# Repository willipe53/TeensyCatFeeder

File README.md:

# TeensyCatFeeder

Instructions for an Teensy 4.0 controller to lock a cover over a catfood dish with an electromagnet when a button is pressed, and to move a servo arm to reveal the catfood (and ring a bell) at a scheduled time in the morning.

This is a project that I originally did using Raspberry Pi, then ported to ESP32, then to Teensy.  Hardware consists of the microcontroller, a 5V relay with a transistor circuit to control the electromagnet, a button, and a small LCD display.

There are three servos connected in an arm that hold the lid (a wood box) over dish with catfood. See [sketch.png](sketch.png).  In the code, the servos are named Shoulder, Elbow and Wrist.  See [ServoControl.ino](ServoControl.ino).  Their relative positions are saved in non-volatile memory on the controller using the [Preferences.h](https://github.com/espressif/arduino-esp32/tree/master/libraries/Preferences) library. See [SavingPrefs.ino](SavingPrefs.ino).

There is only one button, so it is hopelessly overloaded.  A short press either opens the feeder or locks the magnet, depending upon current state.  A long press cycles through current time and feeding time, so they can be set.  You can also connect the feeder to a computer and set these values via the serial monitor.  Sending a `p` over the serial port should show the current values, as well as the following menu:

`o - Open the lid`
`l - Lock or unlock magnet (1 or 0)`
`s - Move shoulder to x`
`e - Move elbow to x`
`w - Move wrist to x`
`j - Save number of jiggles to x`
`t - Save wake time as x (HHMM) - 0 = off`
`d - Save clock date as x (YYYYMMDD)`
`c - Save clock time as x (HHMM)`
`b - Save as new open`
`p - Print all values`

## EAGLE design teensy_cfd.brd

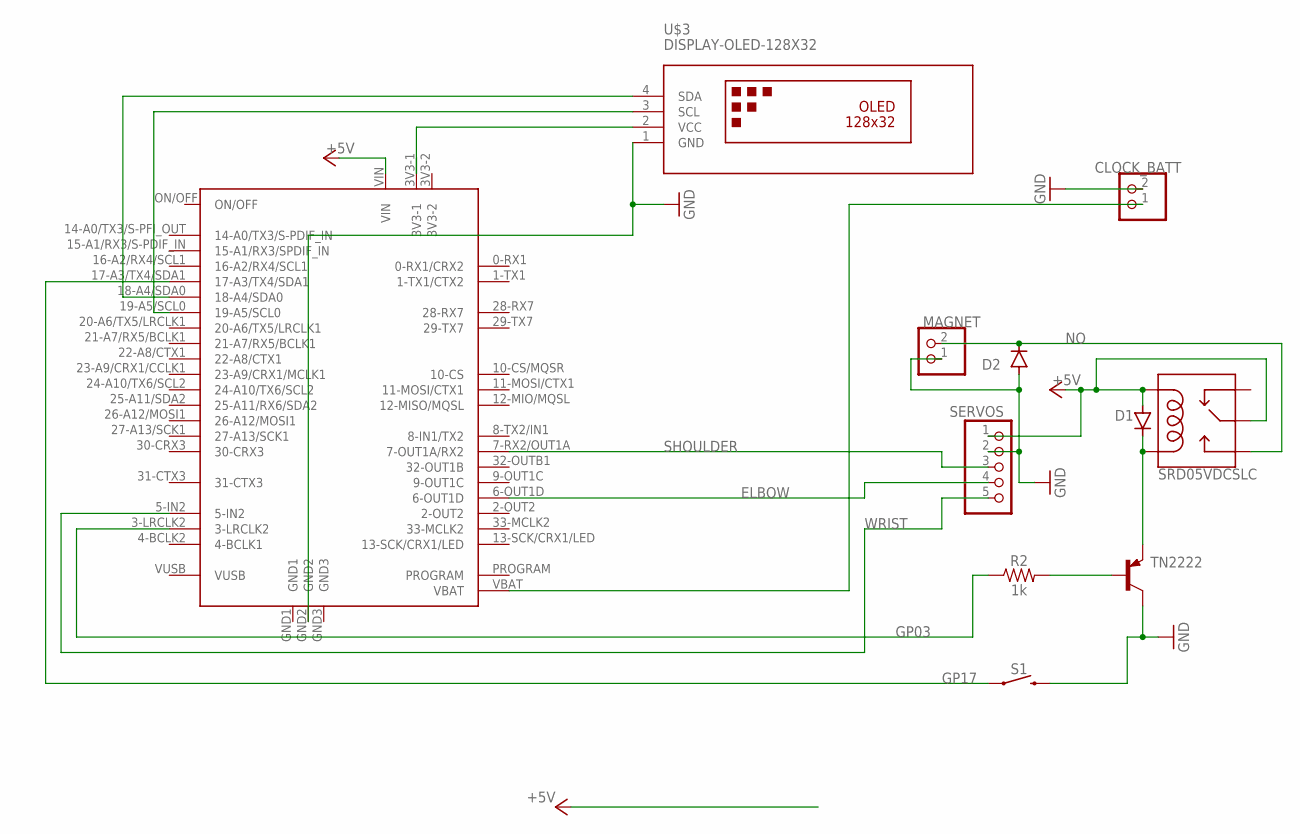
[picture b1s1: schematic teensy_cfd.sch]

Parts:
CLOCK_BATT: PINHD-1X2; 1X02
D1, D2: 1N4004; DO41-10
MAGNET: PINHD-1X2; 1X02
R2: 1k; AXIAL-0.3
S1: MOMENTARY-SWITCH-SPST-PTH-6.0MM; TACTILE_SWITCH_PTH_6.0MM
SERVOS: PINHD-1X5; 1X05
SRD05VDCSLC: RELAYPTH; SRD-05VDC-SL-C
TN2222: TN2222; TO92
U$1: TEENSY40
U$3: DISPLAY-OLED-128X32

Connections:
+5V: D1.A, SERVOS.1, SRD05VDCSLC.COIL1, SRD05VDCSLC.SWCOMMON, U$1.VIN
ELBOW: SERVOS.4, U$1.6-OUT1D
GND: CLOCK_BATT.2, D2.A, MAGNET.1, S1.3 (2), SERVOS.2, TN2222.1 (C), U$1.GND2, U$3.1 (GND)
GP03: R2.P$1 (1), U$1.3-LRCLK2
GP17: S1.1, U$1.17-A3/TX4/SDA1
unnamed: R2.P$2 (2), TN2222.2 (B)
unnamed: D1.C, SRD05VDCSLC.COIL0, TN2222.3 (E)
unnamed: CLOCK_BATT.1, U$1.VBAT
unnamed: U$1.18-A4/SDA0, U$3.4 (SDA)
unnamed: U$1.19-A5/SCL0, U$3.3 (SCL)
unnamed: U$1.3V3-1, U$3.2 (VCC)
NO: D2.C, MAGNET.2, SRD05VDCSLC.SWOPEN
SHOULDER: SERVOS.3, U$1.7-RX2/OUT1A (7-OUT1A/RX2)
WRIST: SERVOS.5, U$1.5-IN2

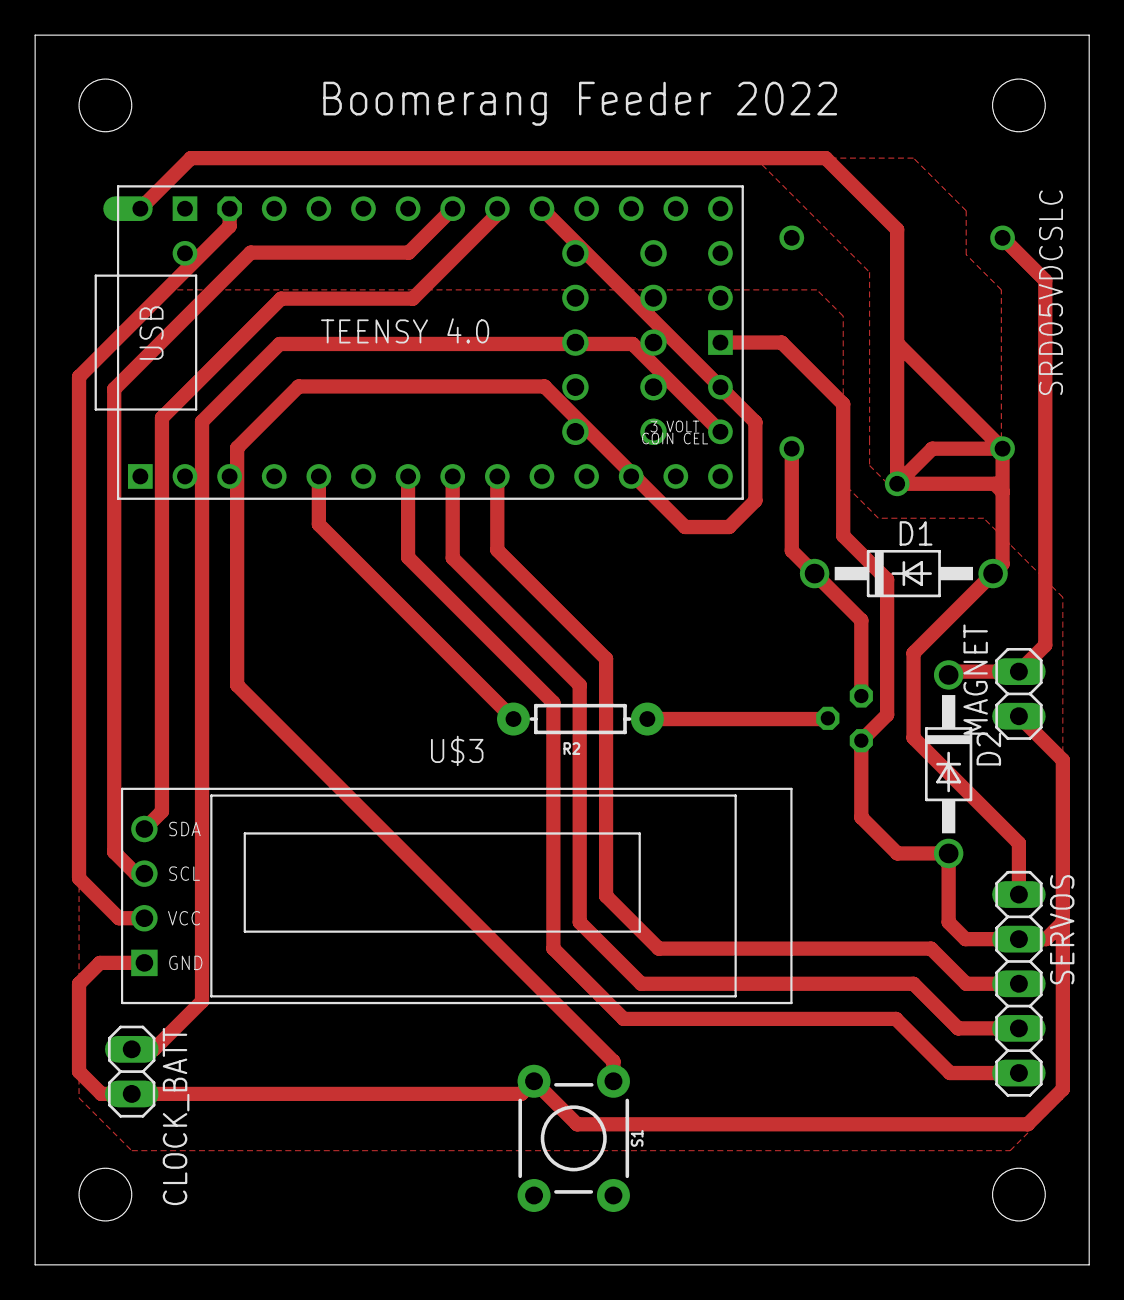
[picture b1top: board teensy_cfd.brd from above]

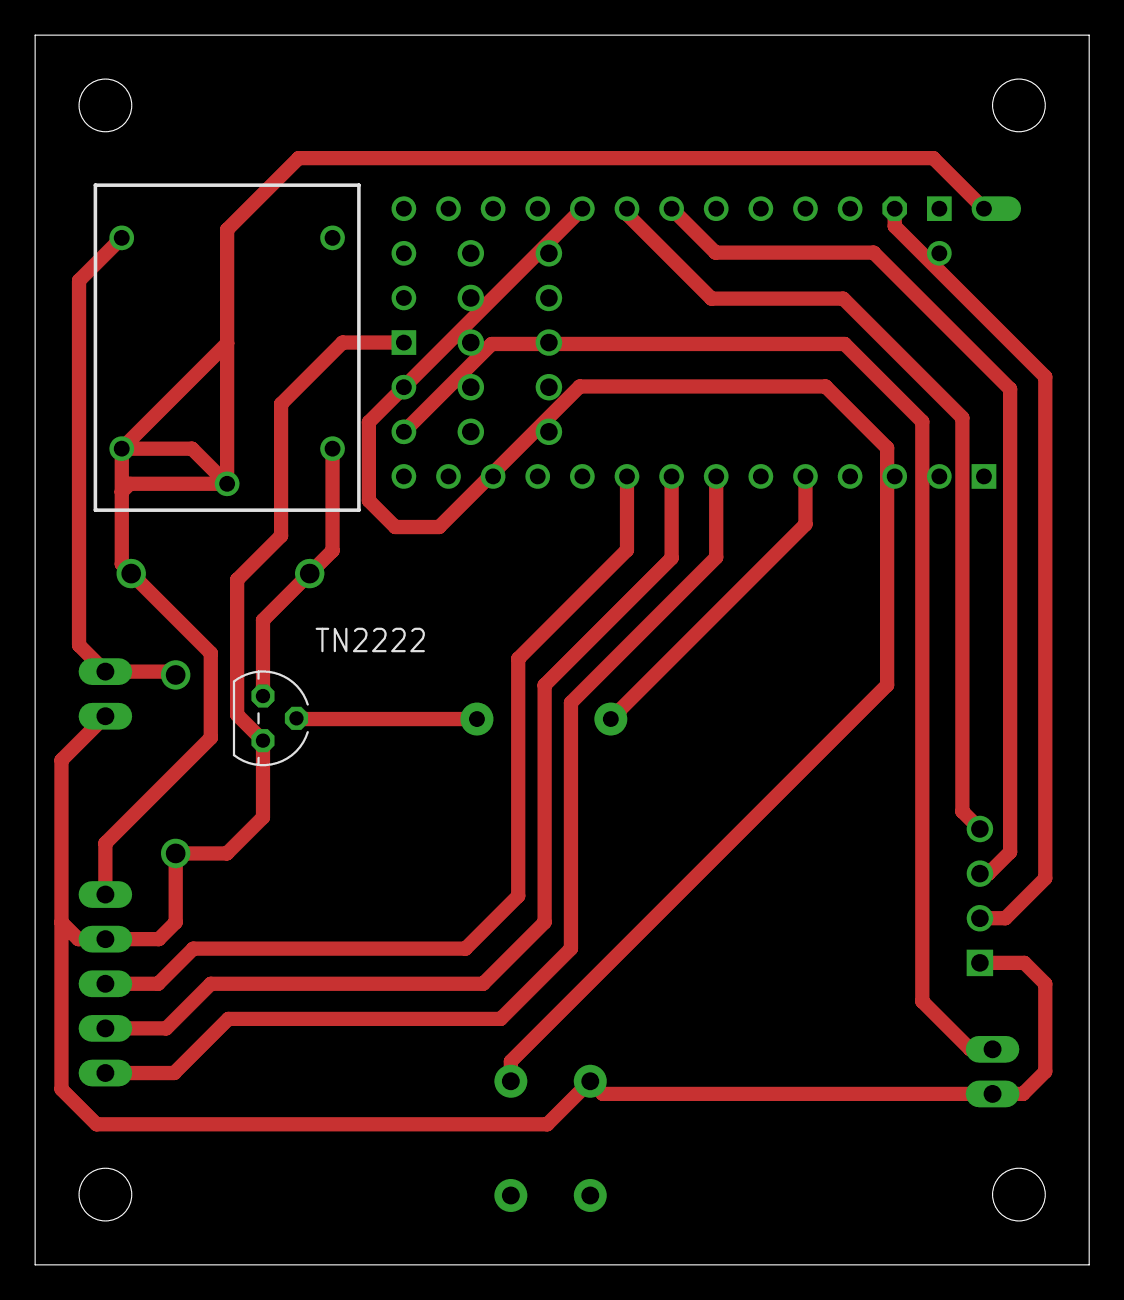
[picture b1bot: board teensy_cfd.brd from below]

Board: 2 copper layers, 60.0 x 70.0 mm, 11 parts (2 on the bottom side), 14 nets.

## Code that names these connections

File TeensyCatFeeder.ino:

#include <EEPROM.h>
#include <TimeLib.h>
#include <Servo.h>
#include <Adafruit_GFX.h>
#include <Adafruit_SSD1306.h>
#include <Wire.h>
#include <EEPROM.h>

#define SCREEN_WIDTH  128 // pixels
#define SCREEN_HEIGHT  32 
#define PRESS_TIME   1000 // milliseconds
#define BUTTON         17 // GPIO
#define MAGNET          3
#define SHOULDER        0 //array index
#define ELBOW           1
#define WRIST           2
#define TS_NONE         0
#define TS_WAKE         1
#define TS_HOUR         2
#define TS_MIN          3
#define DIM_SCREEN     20 //after 20 seconds
 
//default preferences
int servoTop         = 2500; //milliseconds
int servoBottom      = 1400;
int servoMiddle      = 1400;
int servoSide        =  500;
int servoElbowOffset =  250;
int jiggleTimes      =    3;
int wakeTime         =  500; //5AM, wake time of 0 means vacation mode, no feeding

struct Prefs {
  int servoTop;
  int servoBottom;
  int servoMiddle;
  int servoSide;
  int servoElbowOffset;
  int jiggleTimes;
  int wakeTime;
};
Prefs prefs;

Adafruit_SSD1306 display(SCREEN_WIDTH, SCREEN_HEIGHT, &Wire, -1, 1000000);
Servo shoulderServo;
Servo elbowServo;
Servo wristServo;
Servo servoMotor[] = {shoulderServo, elbowServo, wristServo};

int servoPins[]     = {7, 6, 5};
String servoNames[] = {"Shoulder", "Elbow", "Wrist"};
char lastTimeStr[128];
int cursorPos = 130; //just offscreen
int lastButtonState = LOW;
int thisButtonState;
int timeSetMode = TS_NONE;
unsigned long pressedTime  = 0;
unsigned long releasedTime = 0;
unsigned long sleepDisplayAt;
bool servosOn = false;
bool isPressing = false;
bool isLongDetected = false;
bool isLocked = false;
bool displayAwake = true;
bool doneForToday = false;

String inputChars = "olsewjtdcbp";
String outputNames[] = {"Open the lid",                            //o
                        "Lock or unlock magnet (1 or 0)",          //l
                        "Move shoulder to x",                      //s
                        "Move elbow to x",                         //e
                        "Move wrist to x",                         //w
                        "Save number of jiggles to x",             //j
                        "Save wake time as x (HHMM) - 0 = off",    //t
                        "Save clock date as x (YYYYMMDD))",        //d
                        "Save clock time as x (HHMM))",            //c
                        "Save as new open",                        //b
                        "Print all values"};                       //p

void processCommand(String cmd) {
  Serial.printf("Command received: %s\n", cmd.c_str());
  String key = cmd.substring(0,1);
  long valu = cmd.substring(1,cmd.length()-1).toInt();
  if (key.equals("o")) openLid();   
  else if (key.equals("l")) toggleMagnet(valu);            
  else if (key.equals("s")) moveServo(SHOULDER, valu);   
  else if (key.equals("e")) moveServo(ELBOW, valu);   
  else if (key.equals("w")) moveServo(WRIST, valu);   
  else if (key.equals("j")) saveJiggleTimes(valu);   
  else if (key.equals("t")) saveWakeTime(valu);            
  else if (key.equals("d")) resetDateTo(valu);            
  else if (key.equals("c")) resetTimeTo(valu);            
  else if (key.equals("b")) saveNewOpenPosition();   
  else if (key.equals("p")) printValues();            
  else Serial.printf("Unrecognized input: no values will be changed\n");
}

void startDisplayDimmerTimer() {
  sleepDisplayAt = millis() + (DIM_SCREEN * 1000); 
  displayAwake = true;
  Serial.printf("Now: %d, sleep set for: %d\n", millis(), sleepDisplayAt);
}

void resetDateTo(long valu) {
  String cmd = String(valu);
  int yr = cmd.substring(0,4).toInt();
  int mo = cmd.substring(4,6).toInt();
  int dd = cmd.substring(6,8).toInt();  
  setTime(hour(),minute(),0,dd,mo,yr);
}

void resetTimeTo(long valu) {
  String cmd = String(valu);
  int hr = cmd.substring(0,2).toInt();
  int mn = cmd.substring(2,4).toInt();
  setTime(hr,mn,0,day(),month(),year());
//  Serial.printf("valu:%d yr:%d mo%d dd%d hr%d mn%d\n", valu, yr, mo, dd, hr, mn);
}

time_t getTeensy3Time() {
  return Teensy3Clock.get();
}

void toggleMagnet(int valu) {
  digitalWrite(MAGNET, valu);
  isLocked = valu;
  Serial.printf("Reset magnet to %d\n", isLocked);
}

bool isWakeupTime() {
  if (wakeTime == 0) return false;
  if ((hour() == getWakeHour()) && (minute() >= getWakeMin()) && (doneForToday == false)) {
    doneForToday = true;
    return true;
  }
  return false;
}

int getWakeHour() {
  return (wakeTime / 100);
}

int getWakeMin() {
  return (wakeTime % 100);
}

void advanceDigit() {
  if (timeSetMode == TS_HOUR) {
    int hr = hour() + 1;
    if (hr > 24) hr = 1;
    setTime(hr,minute(),0,day(),month(),year());
  } else if (timeSetMode == TS_MIN) {
    int mn = minute() + 1;
    if (mn > 59) mn = 0;
    setTime(hour(),mn,0,day(),month(),year());
  } else if (timeSetMode == TS_WAKE) {
    int wake = getWakeHour() + 1;
    if (wake > 24) wake = 0;
    saveWakeTime(wake*100);  
  }
  Serial.printf("Advancing the setting under the cursor for time item %d.", timeSetMode);
}

void setup()  {
  Serial.begin(9600);
  loadPreferences(true);
  pinMode(BUTTON, INPUT_PULLUP);
  pinMode(MAGNET, OUTPUT);
  for (int i=0; i<3; i++) {
    pinMode(servoPins[i], OUTPUT);
    digitalWrite(servoPins[i], 0);
  }
  toggleMagnet(0);
  setSyncProvider(getTeensy3Time);
  display.begin(SSD1306_SWITCHCAPVCC, 0x3C);
  display.setTextSize(1);
  display.setTextColor(WHITE);
  printValues();
  startDisplayDimmerTimer();
}

void loop() {
  //see if it is time to open the arm
  if (isWakeupTime()) openLid();

  //advance to tomorrow, if an hour past since last feeding
  if (doneForToday && (hour() >= getWakeHour()+1)) doneForToday = false;
  
  //turn off display to avoid burn in
  if (millis() > sleepDisplayAt) displayAwake = false;
  
  //check button
  thisButtonState = digitalRead(BUTTON);
  if (lastButtonState == HIGH && thisButtonState == LOW) {        // button is pressed
    pressedTime = millis();
    isPressing = true;
    isLongDetected = false;
  } else if (lastButtonState == LOW && thisButtonState == HIGH) { // button is released
    isPressing = false;
    releasedTime = millis();
    long pressDuration = releasedTime - pressedTime;
    if (pressDuration < PRESS_TIME) {
      Serial.println("A short press is detected");
      if (!displayAwake) startDisplayDimmerTimer();
      else if (timeSetMode > TS_NONE) advanceDigit();
      else if (isLocked) openLid();
      else toggleMagnet(1);
    }
  }
  if (isPressing == true && isLongDetected == false) {
    long pressDuration = millis() - pressedTime;
    if (pressDuration > PRESS_TIME) {
      Serial.println("A long press is detected");
      isLongDetected = true;
      if (timeSetMode == TS_WAKE) {
        timeSetMode = TS_NONE;
      } else {
        timeSetMode++;
      }
      Serial.printf("Switching to time set mode %d.\n", timeSetMode);
    }
  }
  lastButtonState = thisButtonState;

  //drive display
  display.clearDisplay();
  drawLock();
  drawWake();
  drawTime();
  display.display();

  //manual testing
  if (Serial.available() > 0) processCommand(Serial.readString());

}

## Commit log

2022-03-17 Initial working display and button
2022-03-18 Working servos
2022-03-18 Working servos and prefs
2022-03-19 Scheduler working
2022-03-19 Added onscreen time set
2022-03-19 Added vacation mode
2022-03-19 Added eagle files
2022-09-25 Time set was not working correctly
2022-10-03 Bug in time set
2022-10-09 Added photo of board
2022-10-09 Added pictures
2022-10-09 readme

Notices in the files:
parts and their libraries:
SparkFun-Resistors: Licensing: Creative Commons ShareAlike 4.0 International - https://creativecommons.org/licenses/by-sa/4.0
diy-modules: Released under the Creative Commons Attribution 4.0 International License: http://creativecommons.org/licenses/by/4.0
